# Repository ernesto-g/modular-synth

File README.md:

# Modular synthesizer

Characteristics:

  - Eurorack form factor modules
  - Banana jack connectors
  - 10Vpp audio signals
  - 5V control signals
  - Non standard power connector

# Finished modules

  - [Sequencer](https://github.com/ernesto-g/modular-synth/tree/master/FINISHED/SEQUENCER): 8-step sequencer.
  - [Vintage VCA](https://github.com/ernesto-g/modular-synth/tree/master/FINISHED/VCA): 2-transistor discrete VCA.
  - [Simple VCO](https://github.com/ernesto-g/modular-synth/tree/master/FINISHED/VCO): Triangle and square VCO. 1V/Ocv control voltage.
  - [Slew limiter](https://github.com/ernesto-g/modular-synth/tree/master/FINISHED/SLEW_LIMITER): Slew limiter and LFO
  - [IOs](https://github.com/ernesto-g/modular-synth/tree/master/FINISHED/IOS): Audio line and Eurorack level adapter.
  - [Power Supply](https://github.com/ernesto-g/modular-synth/tree/master/FINISHED/POWER_SUPPLY): Power Supply Board for modules.
  - [Tree](https://github.com/ernesto-g/modular-synth/tree/master/FINISHED/TREE): Banana jack splitter.
  - [Sound Source](https://github.com/ernesto-g/modular-synth/tree/master/FINISHED/SOUND_SOURCE): Macro-oscillator based on Mutable Instruments Braids.
  - [LFOx3](https://github.com/ernesto-g/modular-synth/tree/master/FINISHED/LFOx3): Low frequency oscillator and sequencer.
  - [ATV & Mixer](https://github.com/ernesto-g/modular-synth/tree/master/FINISHED/ATVMixer): Atenuverter X3 and 3-channel mixer.
  - [Simple Sequencer](https://github.com/ernesto-g/modular-synth/tree/master/FINISHED/SIMPLE_SEQUENCER): 4-step sequencer.
  - [Low Pass VCF](https://github.com/ernesto-g/modular-synth/tree/master/FINISHED/VCF): Vactrol VCF.

# Unfinished work

  - Industrial kick
  - Case blueprints
  
# Project structure

Each module has the following structure:

  * Firmware: Microcontroller code (Arduino, Bluepill,etc.)
  * Manual: PDF and DOC file
  * XXXXXXX_modular_PCB: Folder
    * XXXXXXX_modular: Kicad project
    * DIY: PDF files for schematic, PCB and front panel
  * Front Panel Blueprint: Corel Draw files

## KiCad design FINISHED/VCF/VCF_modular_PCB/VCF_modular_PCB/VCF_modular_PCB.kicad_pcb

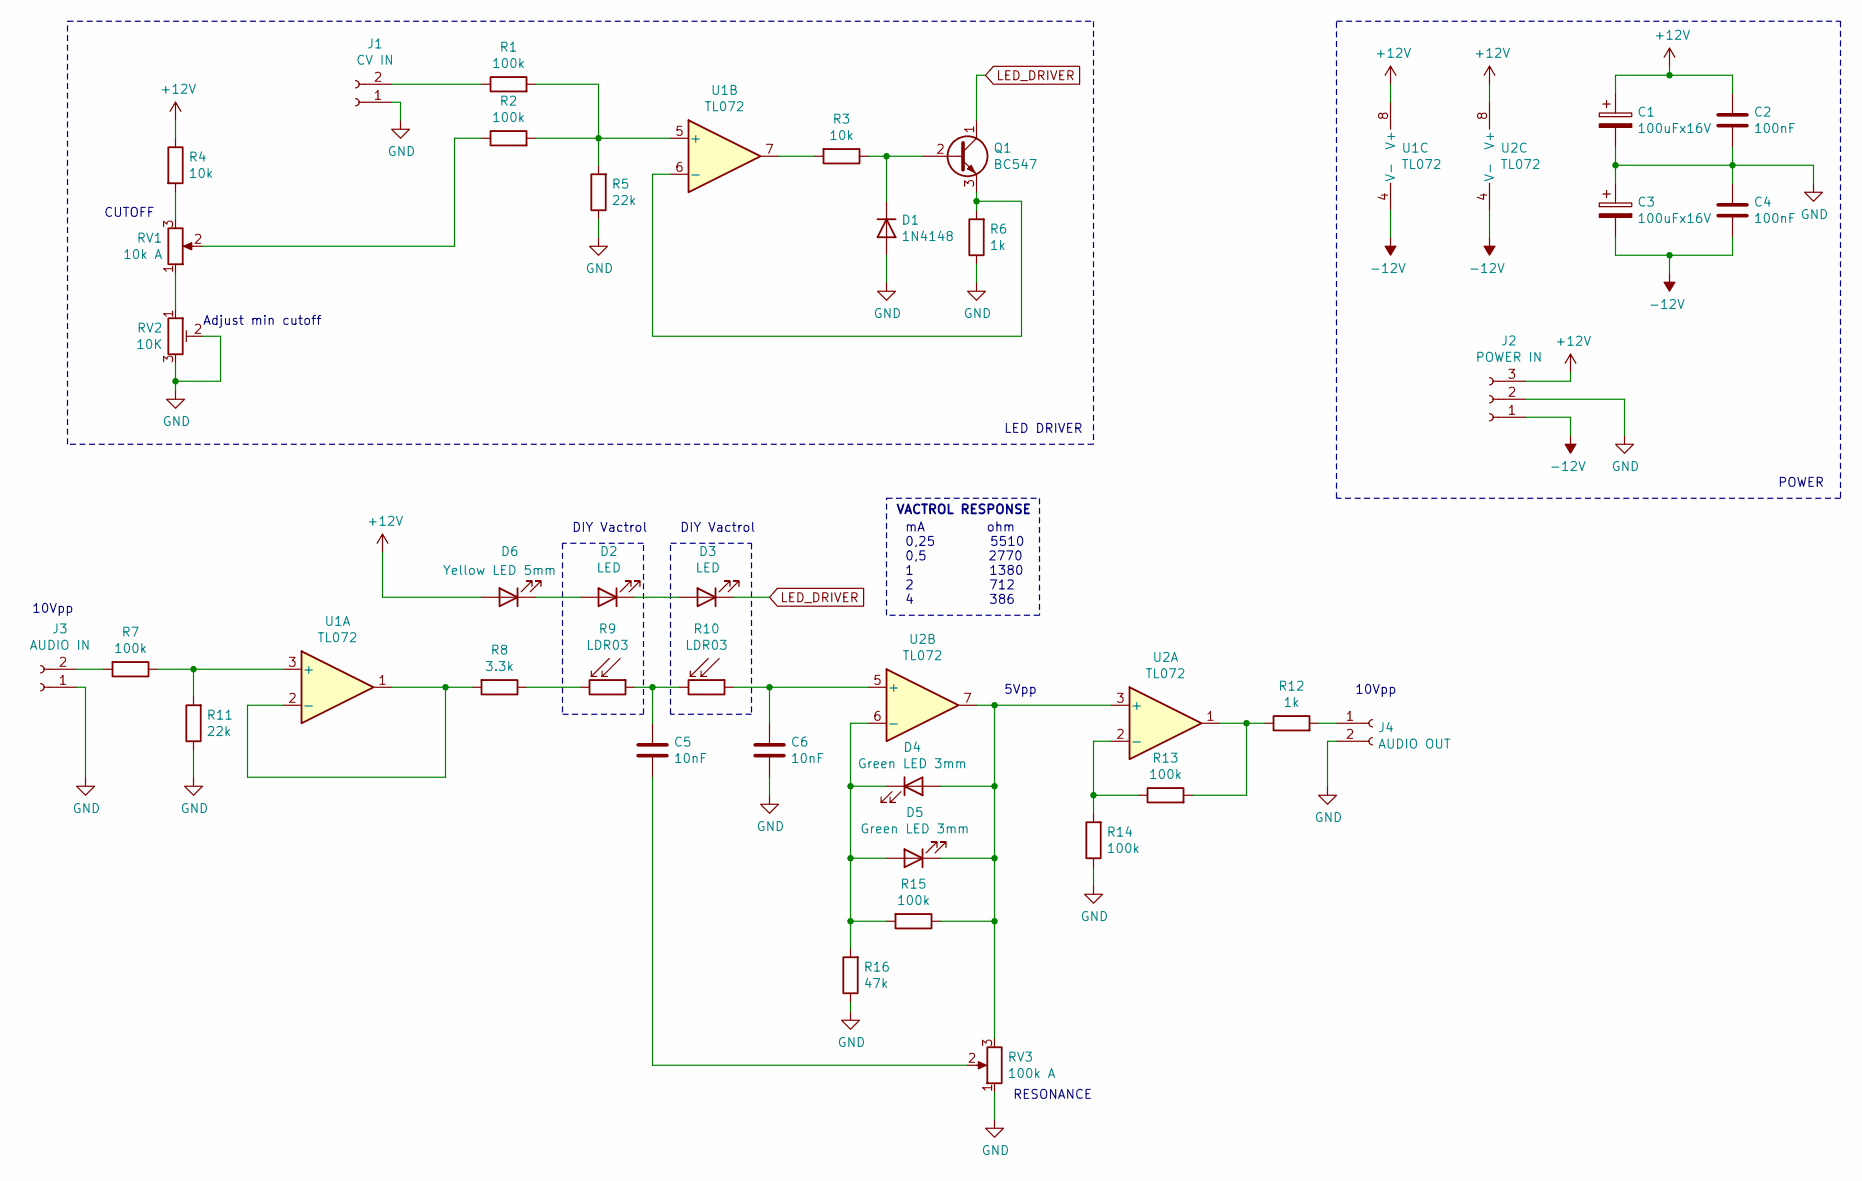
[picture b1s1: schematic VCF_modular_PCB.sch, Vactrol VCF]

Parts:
C1, C3: 100uFx16V; CP_Radial_D6.3mm_P2.50mm
C2, C4: 100nF; C_Disc_D4.7mm_W2.5mm_P5.00mm
C5, C6: 10nF; C_Disc_D4.7mm_W2.5mm_P5.00mm
D1: 1N4148; D_DO-35_SOD27_P7.62mm_Horizontal
D2, D3: LED; LED_D5.0mm_Horizontal_O3.81mm_Z3.0mm
D4, D5: Green LED 3mm; LED_D3.0mm_FlatTop
D6: Yellow LED 5mm; LED_D5.0mm
J1: CV IN; Molex_KK-6410-02_02x2.54mm_Straight
J2: POWER IN; Molex_KK-6410-03_03x2.54mm_Straight
J3: AUDIO IN; Molex_KK-6410-02_02x2.54mm_Straight
J4: AUDIO OUT; Molex_KK-6410-02_02x2.54mm_Straight
Q1: BC547; TO-92_Inline_Wide
R1, R2, R7, R13, R14, R15: 100k; R_Axial_DIN0204_L3.6mm_D1.6mm_P7.62mm_Horizontal
R3, R4: 10k; R_Axial_DIN0204_L3.6mm_D1.6mm_P7.62mm_Horizontal
R5, R11: 22k; R_Axial_DIN0204_L3.6mm_D1.6mm_P7.62mm_Horizontal
R6, R12: 1k; R_Axial_DIN0204_L3.6mm_D1.6mm_P7.62mm_Horizontal
R8: 3.3k; R_Axial_DIN0204_L3.6mm_D1.6mm_P7.62mm_Horizontal
R9, R10: LDR03; Resistor_LDR_Vertical_5.2x5.2_RM3.5
R16: 47k; R_Axial_DIN0204_L3.6mm_D1.6mm_P7.62mm_Horizontal
RV1: 10k A; Potentiometer_Piher_PC-16_Single_Vertical
RV2: 10K; Potentiometer_Trimmer_ACP_CA6v_Horizontal
RV3: 100k A; Potentiometer_Piher_PC-16_Single_Vertical
U1, U2: TL072; DIP-8_W7.62mm_LongPads

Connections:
+12V: C1.1, C2.1, D6.2 (A), J2.3, R4.1, U1.8 (V+), U2.8 (V+)
-12V: C3.2, C4.2, J2.1, U1.4 (V-), U2.4 (V-)
GND: C1.2, C2.2, C3.1, C4.1, C6.2, D1.2 (A), J1.1, J2.2, J3.1, J4.2, R5.1, R6.1, R11.1, R14.1, R16.1, RV2.2, RV2.3, RV3.1
LED_DRIVER: D3.1 (K), Q1.1 (C)
unnamed: C5.1, R9.1, R10.2
unnamed: C5.2, RV3.2
unnamed: C6.1, R10.1, U2.5 (+)
unnamed: D1.1 (K), Q1.2 (B), R3.1
unnamed: D2.1 (K), D3.2 (A)
unnamed: D2.2 (A), D6.1 (K)
unnamed: D4.1 (K), D5.2 (A), R15.2, R16.2, U2.6 (-)
unnamed: D4.2 (A), D5.1 (K), R15.1, RV3.3, U2.3 (+), U2.7
unnamed: J1.2, R1.1
unnamed: J3.2, R7.2
unnamed: J4.1, R12.2
unnamed: Q1.3 (E), R6.2, U1.6 (-)
unnamed: R1.2, R2.2, R5.2, U1.5 (+)
unnamed: R2.1, RV1.2
unnamed: R3.2, U1.7
unnamed: R4.2, RV1.3
unnamed: R8.1, R9.2
unnamed: R8.2, U1.1, U1.2 (-)
unnamed: R7.1, R11.2, U1.3 (+)
unnamed: R12.1, R13.2, U2.1
unnamed: R13.1, R14.2, U2.2 (-)
unnamed: RV1.1, RV2.1

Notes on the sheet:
RESONANCE
DIY Vactrol
CUTOFF
LED DRIVER
POWER
Adjust min cutoff
mA ohm 0,25 5510 0,5 2770 1 1380 2 712 4 386
VACTROL RESPONSE
5Vpp
10Vpp

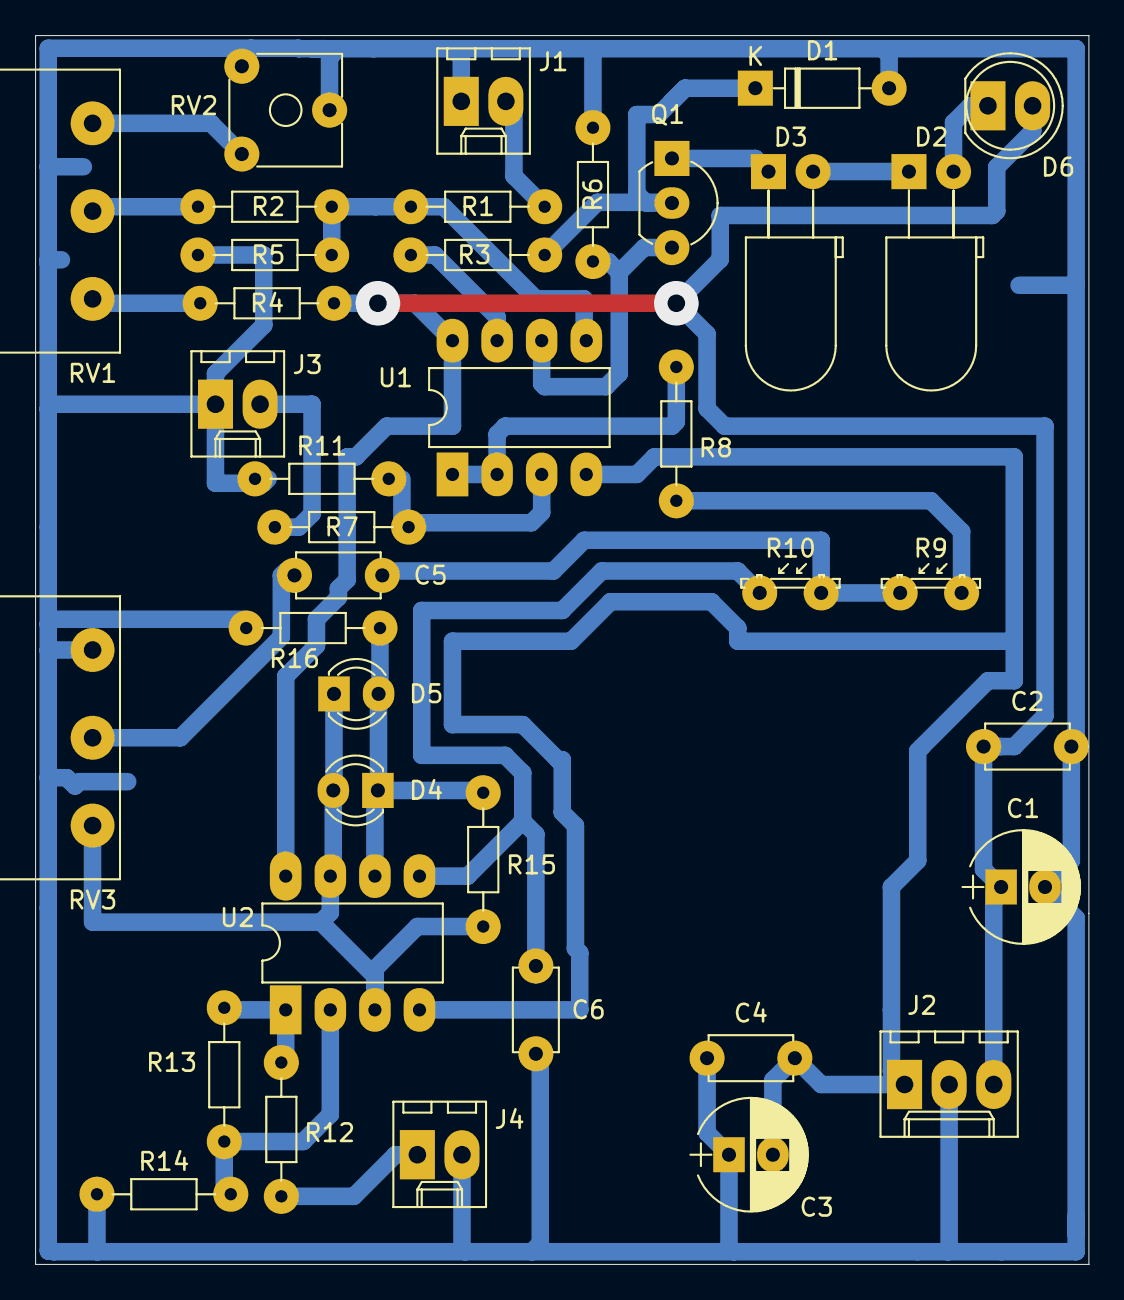
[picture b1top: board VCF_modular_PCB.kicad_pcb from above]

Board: 2 copper layers, 60.0 x 70.0 mm, 38 parts (0 on the bottom side), 26 nets.

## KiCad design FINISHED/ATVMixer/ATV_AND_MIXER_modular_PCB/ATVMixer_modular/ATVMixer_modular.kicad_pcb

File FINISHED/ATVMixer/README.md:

# Atenuverters & 3-channel mixer

Characteristics:

  - Format: Eurorack
  - Dimensions: 8HP, 60mm deep
  - 10Vpp audio signals

# Project structure

  * ATV_AND_MIXER_modular_PCB: Folder
    * ATV_AND_MIXER_modular: Kicad project
    * DIY: PDF files for schematic, PCB and front panel
  * Front Panel Blueprint: Corel Draw files

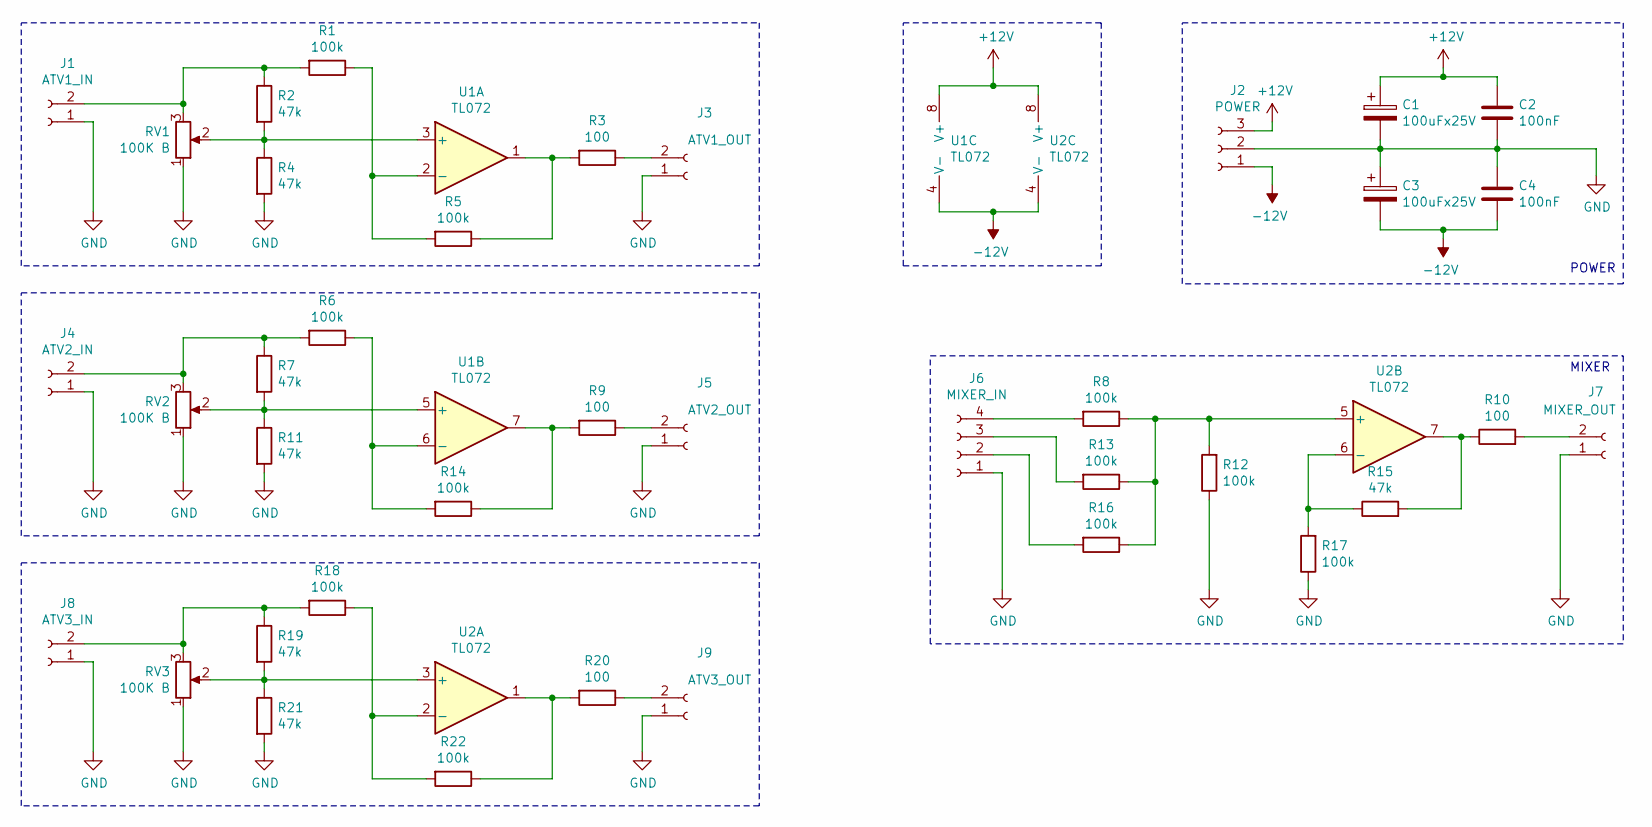
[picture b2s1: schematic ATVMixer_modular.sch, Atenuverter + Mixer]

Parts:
C1, C3: 100uFx25V; CP_Radial_D6.3mm_P2.50mm
C2, C4: 100nF; C_Disc_D4.3mm_W1.9mm_P5.00mm
J1: ATV1_IN; Molex_KK-6410-02_02x2.54mm_Straight
J2: POWER; Molex_KK-6410-03_03x2.54mm_Straight
J3: ATV1_OUT; Molex_KK-6410-02_02x2.54mm_Straight
J4: ATV2_IN; Molex_KK-6410-02_02x2.54mm_Straight
J5: ATV2_OUT; Molex_KK-6410-02_02x2.54mm_Straight
J6: MIXER_IN; Molex_KK-6410-04_04x2.54mm_Straight
J7: MIXER_OUT; Molex_KK-6410-02_02x2.54mm_Straight
J8: ATV3_IN; Molex_KK-6410-02_02x2.54mm_Straight
J9: ATV3_OUT; Molex_KK-6410-02_02x2.54mm_Straight
R1, R5, R6, R8, R12, R13, R14, R16, R17, R18, R22: 100k; R_Axial_DIN0204_L3.6mm_D1.6mm_P7.62mm_Horizontal
R2, R4, R7, R11, R15, R19, R21: 47k; R_Axial_DIN0204_L3.6mm_D1.6mm_P7.62mm_Horizontal
R3, R9, R10, R20: 100; R_Axial_DIN0204_L3.6mm_D1.6mm_P7.62mm_Horizontal
RV1, RV2, RV3: 100K B; Potentiometer_Piher_PC-16_Single_Vertical
U1, U2: TL072; DIP-8_W7.62mm_LongPads

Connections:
+12V: C1.1, C2.1, J2.3, U1.8 (V+), U2.8 (V+)
-12V: C3.2, C4.2, J2.1, U1.4 (V-), U2.4 (V-)
GND: C1.2, C2.2, C3.1, C4.1, J1.1, J2.2, J3.1, J4.1, J5.1, J6.1, J7.1, J8.1, J9.1, R4.2, R11.2, R12.1, R17.1, R21.2, RV1.1, RV2.1, RV3.1
unnamed: J1.2, R1.2, R2.1, RV1.3
unnamed: J3.2, R3.1
unnamed: J4.2, R6.2, R7.1, RV2.3
unnamed: J5.2, R9.1
unnamed: J6.2, R16.2
unnamed: J6.3, R13.2
unnamed: J6.4, R8.2
unnamed: J7.2, R10.2
unnamed: J8.2, R18.2, R19.1, RV3.3
unnamed: J9.2, R20.1
unnamed: R1.1, R5.2, U1.2 (-)
unnamed: R2.2, R4.1, RV1.2, U1.3 (+)
unnamed: R3.2, R5.1, U1.1
unnamed: R10.1, R15.2, U2.7
unnamed: R7.2, R11.1, RV2.2, U1.5 (+)
unnamed: R8.1, R12.2, R13.1, R16.1, U2.5 (+)
unnamed: R9.2, R14.1, U1.7
unnamed: R6.1, R14.2, U1.6 (-)
unnamed: R15.1, R17.2, U2.6 (-)
unnamed: R18.1, R22.2, U2.2 (-), U2.752
unnamed: R19.2, R21.1, RV3.2, U2.3 (+)
unnamed: R20.2, R22.1, U2.1

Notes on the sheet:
MIXER
POWER

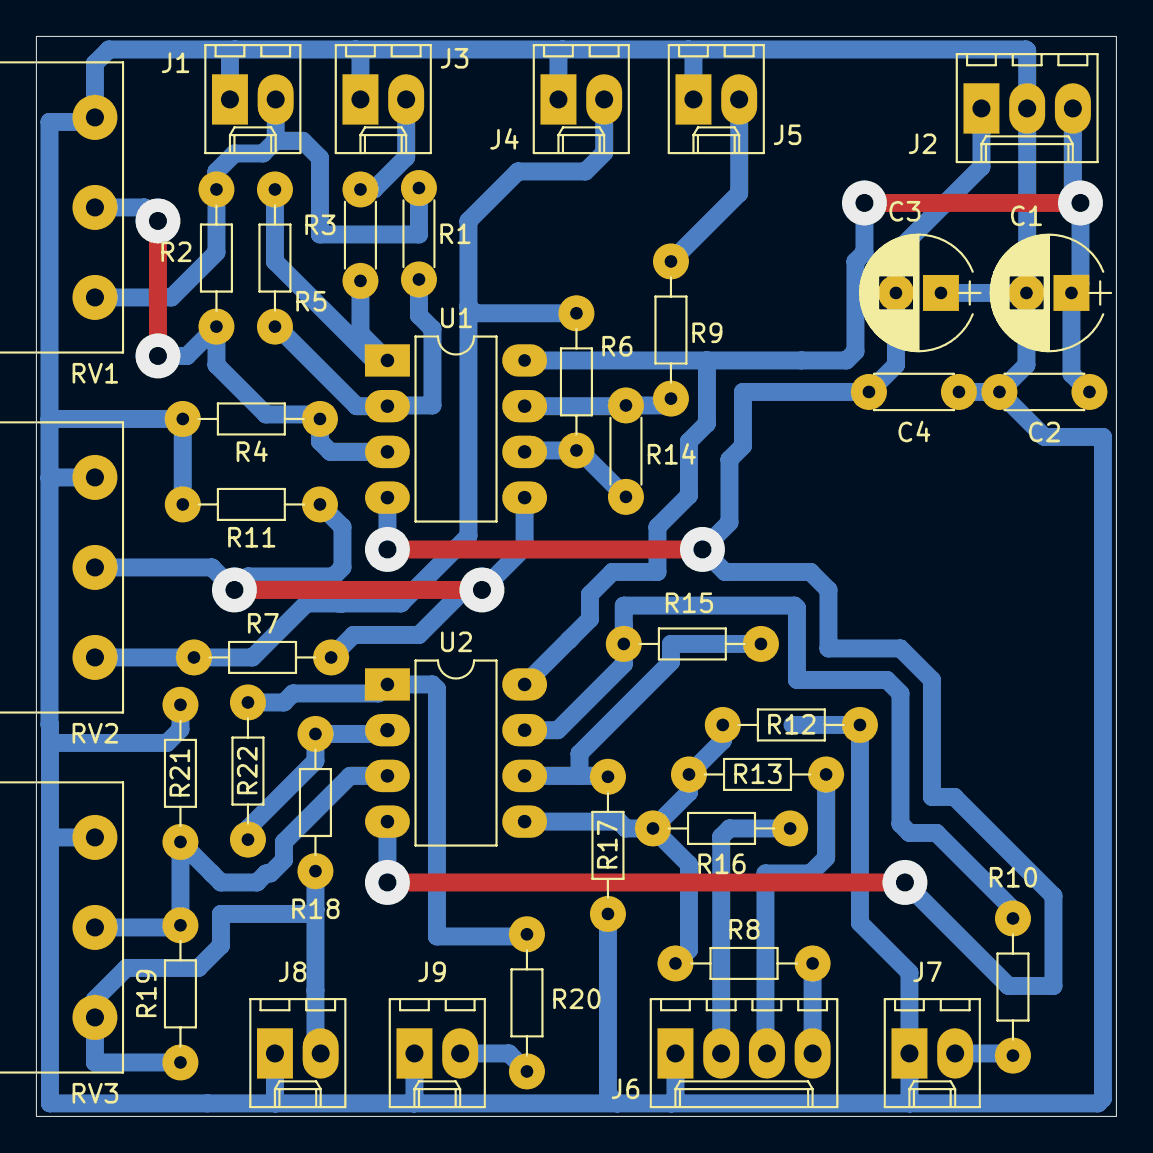
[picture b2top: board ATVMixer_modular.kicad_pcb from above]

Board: 2 copper layers, 60.0 x 60.0 mm, 40 parts (0 on the bottom side), 25 nets.

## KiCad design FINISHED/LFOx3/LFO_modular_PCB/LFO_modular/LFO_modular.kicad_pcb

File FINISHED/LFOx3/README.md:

# LFOx3: Low frequency oscillator
LFOx3 is a 3 channel digital low frequency oscillator module.

Characteristics:

  - Format: Eurorack
  - Dimensions: 8HP, 60mm deep
  - 10Vpp audio signals
  - 5V control signals
  - 5 Waveforms
  - 105sec to 150Hz range.
  - 10kHz, 8-bit audio processing
  - Beginning of cycle Output.

Download [manual](https://github.com/ernesto-g/modular-synth/raw/master/FINISHED/LFOx3/Manual/LFOx3%20Manual.pdf)   
 
# Project structure

  * Firmware: Code for Arduino nano
  * Manual: PDF and DOC file
  * LFO_modular_PCB: Folder
    * LFO_modular: Kicad project
    * DIY: PDF files for schematic, PCB and front panel
  * Front Panel Blueprint: Corel Draw files

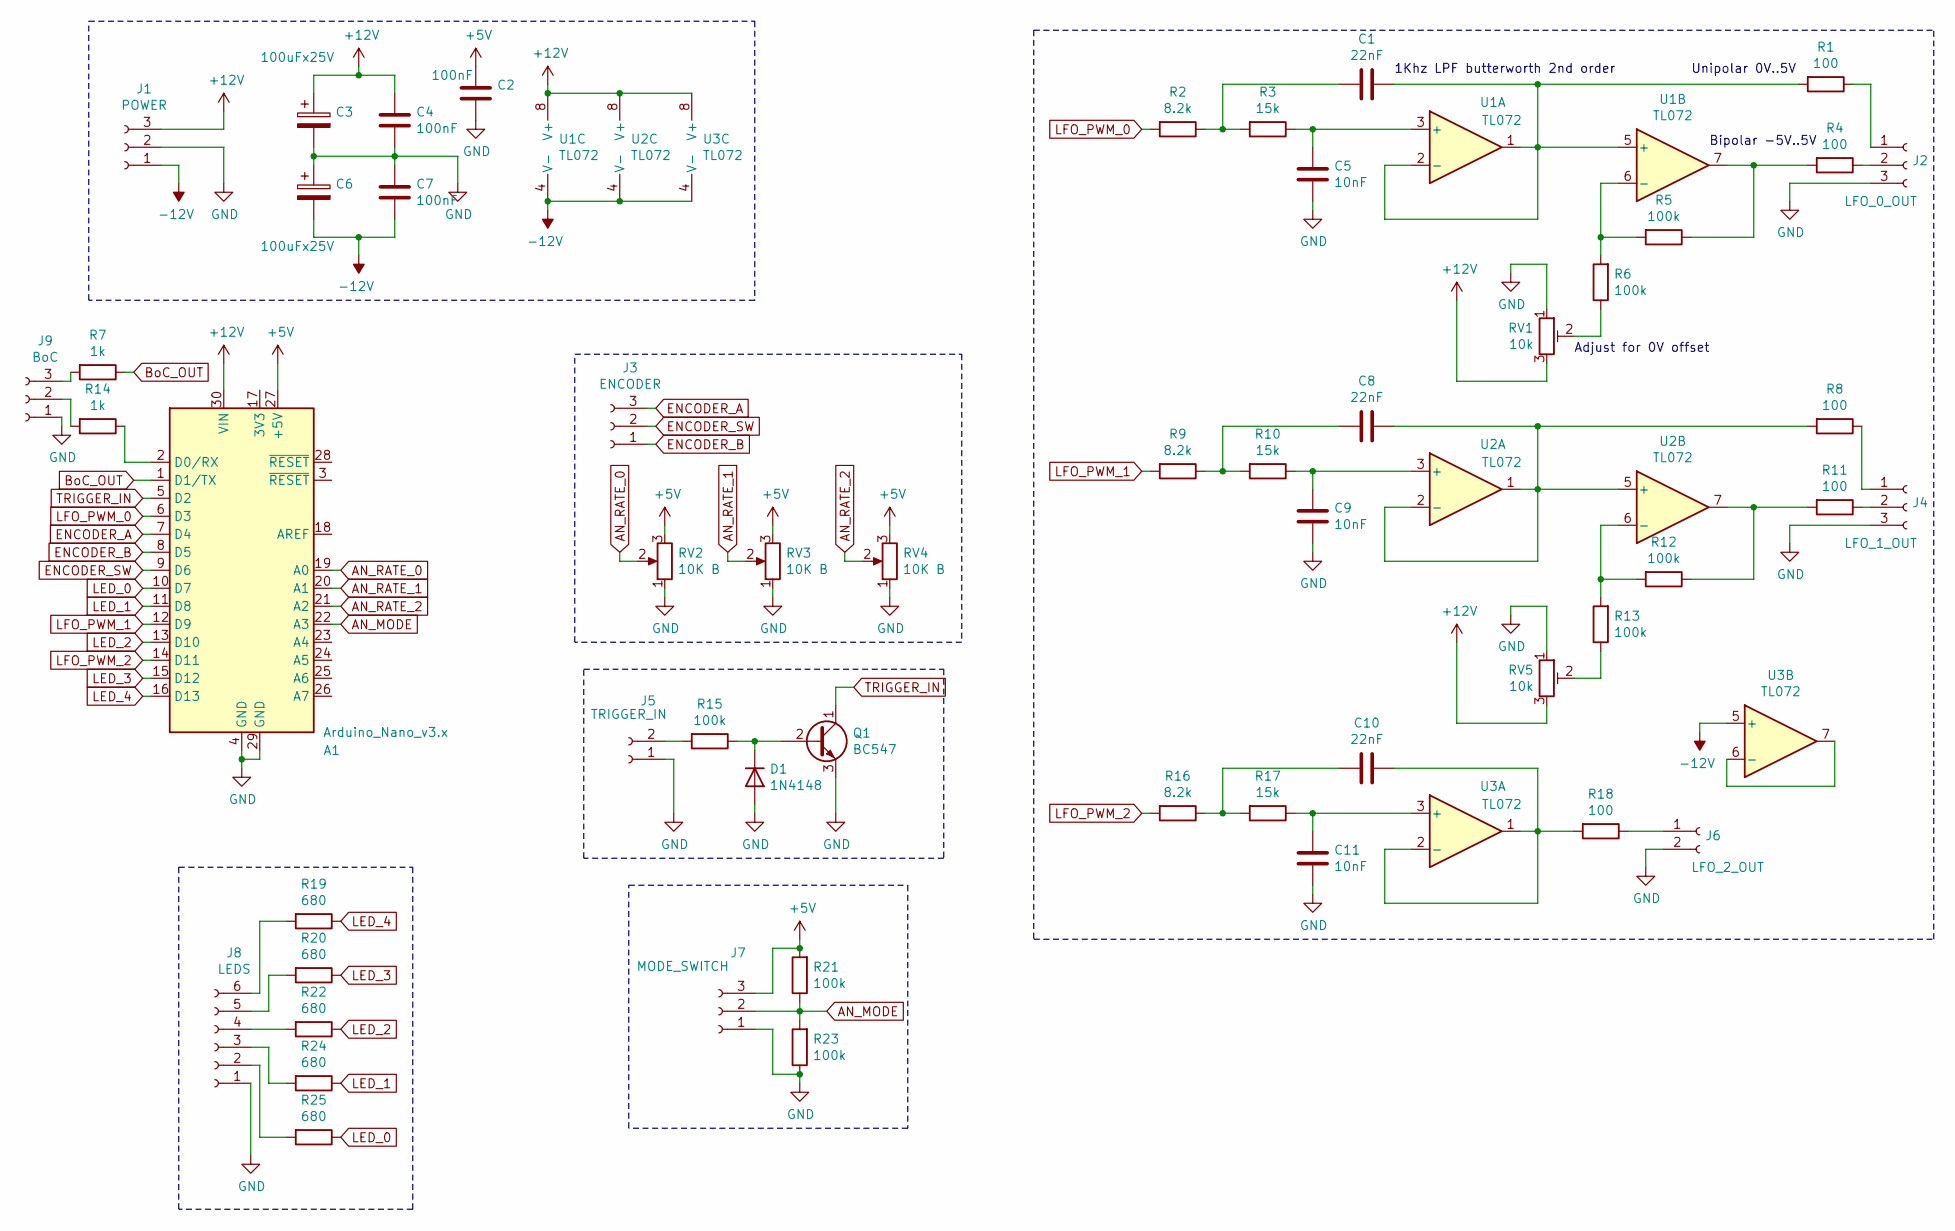
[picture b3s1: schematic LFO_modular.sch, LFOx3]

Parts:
A1: Arduino_Nano_v3.x; Arduino_Nano
C1, C8, C10: 22nF; C_Disc_D4.7mm_W2.5mm_P5.00mm
C2, C4, C7: 100nF; C_Disc_D4.7mm_W2.5mm_P5.00mm
C3, C6: 100uFx25V; CP_Radial_D6.3mm_P2.50mm
C5, C9, C11: 10nF; C_Disc_D4.7mm_W2.5mm_P5.00mm
D1: 1N4148; D_DO-35_SOD27_P7.62mm_Horizontal
J1: POWER; Molex_KK-6410-03_03x2.54mm_Straight
J2: LFO_0_OUT; Molex_KK-6410-03_03x2.54mm_Straight
J3: ENCODER; Molex_KK-6410-03_03x2.54mm_Straight
J4: LFO_1_OUT; Molex_KK-6410-03_03x2.54mm_Straight
J5: TRIGGER_IN; Molex_KK-6410-02_02x2.54mm_Straight
J6: LFO_2_OUT; Molex_KK-6410-02_02x2.54mm_Straight
J7: MODE_SWITCH; Molex_KK-6410-03_03x2.54mm_Straight
J8: LEDS; Molex_KK-6410-06_06x2.54mm_Straight
J9: BoC; Molex_KK-6410-03_03x2.54mm_Straight
Q1: BC547; TO-92_HandSolder
R1, R4, R8, R11, R18: 100; R_Axial_DIN0204_L3.6mm_D1.6mm_P7.62mm_Horizontal
R2, R9, R16: 8.2k; R_Axial_DIN0204_L3.6mm_D1.6mm_P7.62mm_Horizontal
R3, R10, R17: 15k; R_Axial_DIN0204_L3.6mm_D1.6mm_P7.62mm_Horizontal
R5, R6, R12, R13, R15, R21, R23: 100k; R_Axial_DIN0204_L3.6mm_D1.6mm_P7.62mm_Horizontal
R7, R14: 1k; R_Axial_DIN0204_L3.6mm_D1.6mm_P7.62mm_Horizontal
R19, R20, R22, R24, R25: 680; R_Axial_DIN0204_L3.6mm_D1.6mm_P7.62mm_Horizontal
RV1, RV5: 10k; Potentiometer_Trimmer_ACP_CA6v_Horizontal
RV2, RV3, RV4: 10K B; Potentiometer_Piher_PC-16_Single_Vertical
U1, U2, U3: TL072; DIP-8_W7.62mm_LongPads

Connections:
+5V: A1.27 (+5V), C2.1, J7.3, R21.2, RV2.3, RV3.3, RV4.3
+12V: A1.30 (VIN), C3.1, C4.1, J1.3, RV1.3, RV5.3, U1.8 (V+), U2.8 (V+), U3.8 (V+)
-12V: C6.2, C7.2, J1.1, U1.4 (V-), U2.4 (V-), U3.4 (V-), U3.5 (+)
AN_MODE: A1.22 (A3), J7.2, R21.1, R23.2
AN_RATE_0: A1.19 (A0), RV2.2
AN_RATE_1: A1.20 (A1), RV3.2
AN_RATE_2: A1.21 (A2), RV4.2
ENCODER_A: A1.7 (D4), J3.3
ENCODER_B: A1.8 (D5), J3.1
ENCODER_SW: A1.9 (D6), J3.2
GND: A1.4 (GND), A1.29 (GND), C2.2, C3.2, C4.2, C5.2, C6.1, C7.1, C9.2, C11.2, D1.2 (A), J1.2, J2.3, J4.3, J5.1, J6.2, J7.1, J8.1, J9.1, Q1.3 (E), R23.1, RV1.1, RV2.1, RV3.1, RV4.1, RV5.1
LED_0: A1.10 (D7), R25.1
LED_1: A1.11 (D8), R24.1
LED_2: A1.13 (D10), R22.1
LED_3: A1.15 (D12), R20.1
LED_4: A1.16 (D13), R19.1
LFO_PWM_0: A1.6 (D3), R2.2
LFO_PWM_1: A1.12 (D9), R9.2
LFO_PWM_2: A1.14 (D11), R16.2
unnamed: A1.1 (D1/TX), R7.1
unnamed: A1.2 (D0/RX), R14.1
unnamed: C1.1, R1.2, U1.1, U1.2 (-), U1.5 (+)
unnamed: C1.2, R2.1, R3.2
unnamed: C5.1, R3.1, U1.3 (+)
unnamed: C8.1, R8.2, U2.1, U2.2 (-), U2.5 (+)
unnamed: C8.2, R9.1, R10.2
unnamed: C9.1, R10.1, U2.3 (+)
unnamed: C10.1, R18.2, U3.1, U3.2 (-)
unnamed: C10.2, R16.1, R17.2
unnamed: C11.1, R17.1, U3.3 (+)
unnamed: D1.1 (K), Q1.2 (B), R15.1
unnamed: J2.1, R1.1
unnamed: J2.2, R4.1
unnamed: J4.1, R8.1
unnamed: J4.2, R11.1
unnamed: J5.2, R15.2
unnamed: J6.1, R18.1
unnamed: J8.2, R25.2
unnamed: J8.3, R24.2
unnamed: J8.4, R22.2
unnamed: J8.5, R20.2
unnamed: J8.6, R19.2
unnamed: J9.2, R14.2
unnamed: J9.3, R7.2
unnamed: R4.2, R5.1, U1.7
unnamed: R5.2, R6.2, U1.6 (-)
unnamed: R6.1, RV1.2
unnamed: R11.2, R12.1, U2.7
unnamed: R12.2, R13.2, U2.6 (-)
unnamed: R13.1, RV5.2
unnamed: U3.6 (-), U3.7
TRIGGER_IN: A1.5 (D2), Q1.1 (C)

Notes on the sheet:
Unipolar 0V..5V
Bipolar -5V..5V
1Khz LPF butterworth 2nd order
Adjust for 0V offset

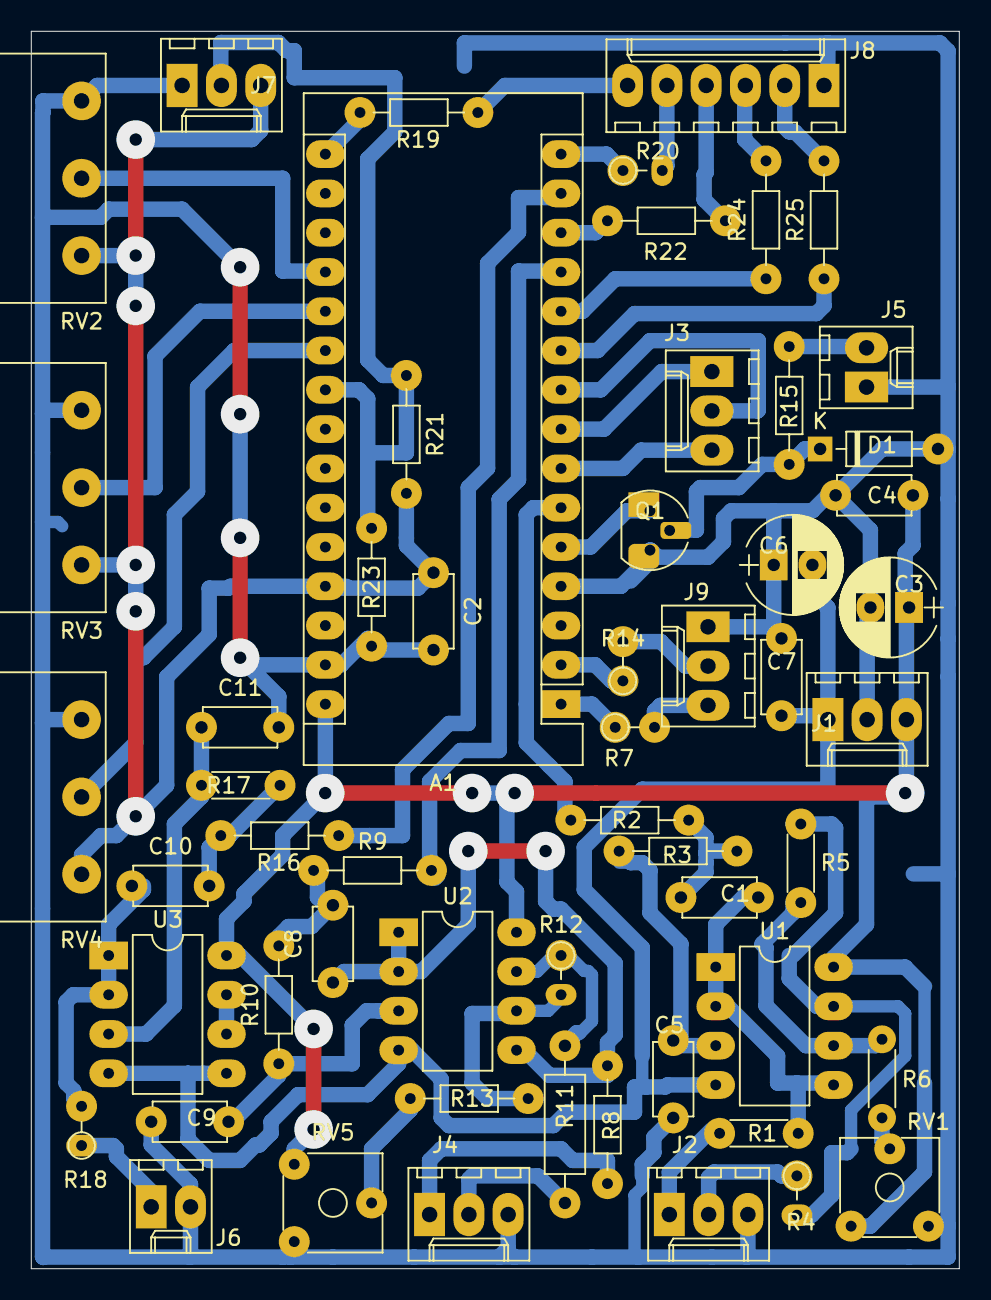
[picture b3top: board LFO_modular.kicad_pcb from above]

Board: 2 copper layers, 60.0 x 80.0 mm, 56 parts (0 on the bottom side), 52 nets.

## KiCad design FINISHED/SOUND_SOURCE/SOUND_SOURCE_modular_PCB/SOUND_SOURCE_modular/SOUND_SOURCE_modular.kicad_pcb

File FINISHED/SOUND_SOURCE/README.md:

# Sound Source: Macro-oscillator
Sound Source is a voltage-controlled monophonic digital oscillator. Each algorithm is controlled by two continuously variable parameters, TIMBRE and COLOR, both of them voltage controllable.

This project is based on Mutable Intruments [Braids](https://mutable-instruments.net/modules/braids). 
The code was adapted for [Blue Pill](https://stm32-base.org/boards/STM32F103C8T6-Blue-Pill.html) microcontroller.

Characteristics:

  - Format: Eurorack
  - Dimensions: 12HP, 80mm deep
  - 10Vpp audio signals
  - 5V control signals
  - 43 Waveforms
  - 96kHz, 8-bit audio processing
  - 12-bit CV capture.

Download [manual](https://github.com/ernesto-g/modular-synth/raw/master/FINISHED/SOUND_SOURCE/Manual/Sound%20Source%20Manual.pdf)   
 
# Project structure

  * Firmware: Code for Blue Pill using ST Cube IDE
  * Manual: PDF and DOC file
  * SOUND_SOURCE_modular_PCB: Folder
    * SOUND_SOURCE_modular: Kicad project
    * DIY: PDF files for schematic, PCB and front panel
  * Front Panel Blueprint: Corel Draw files

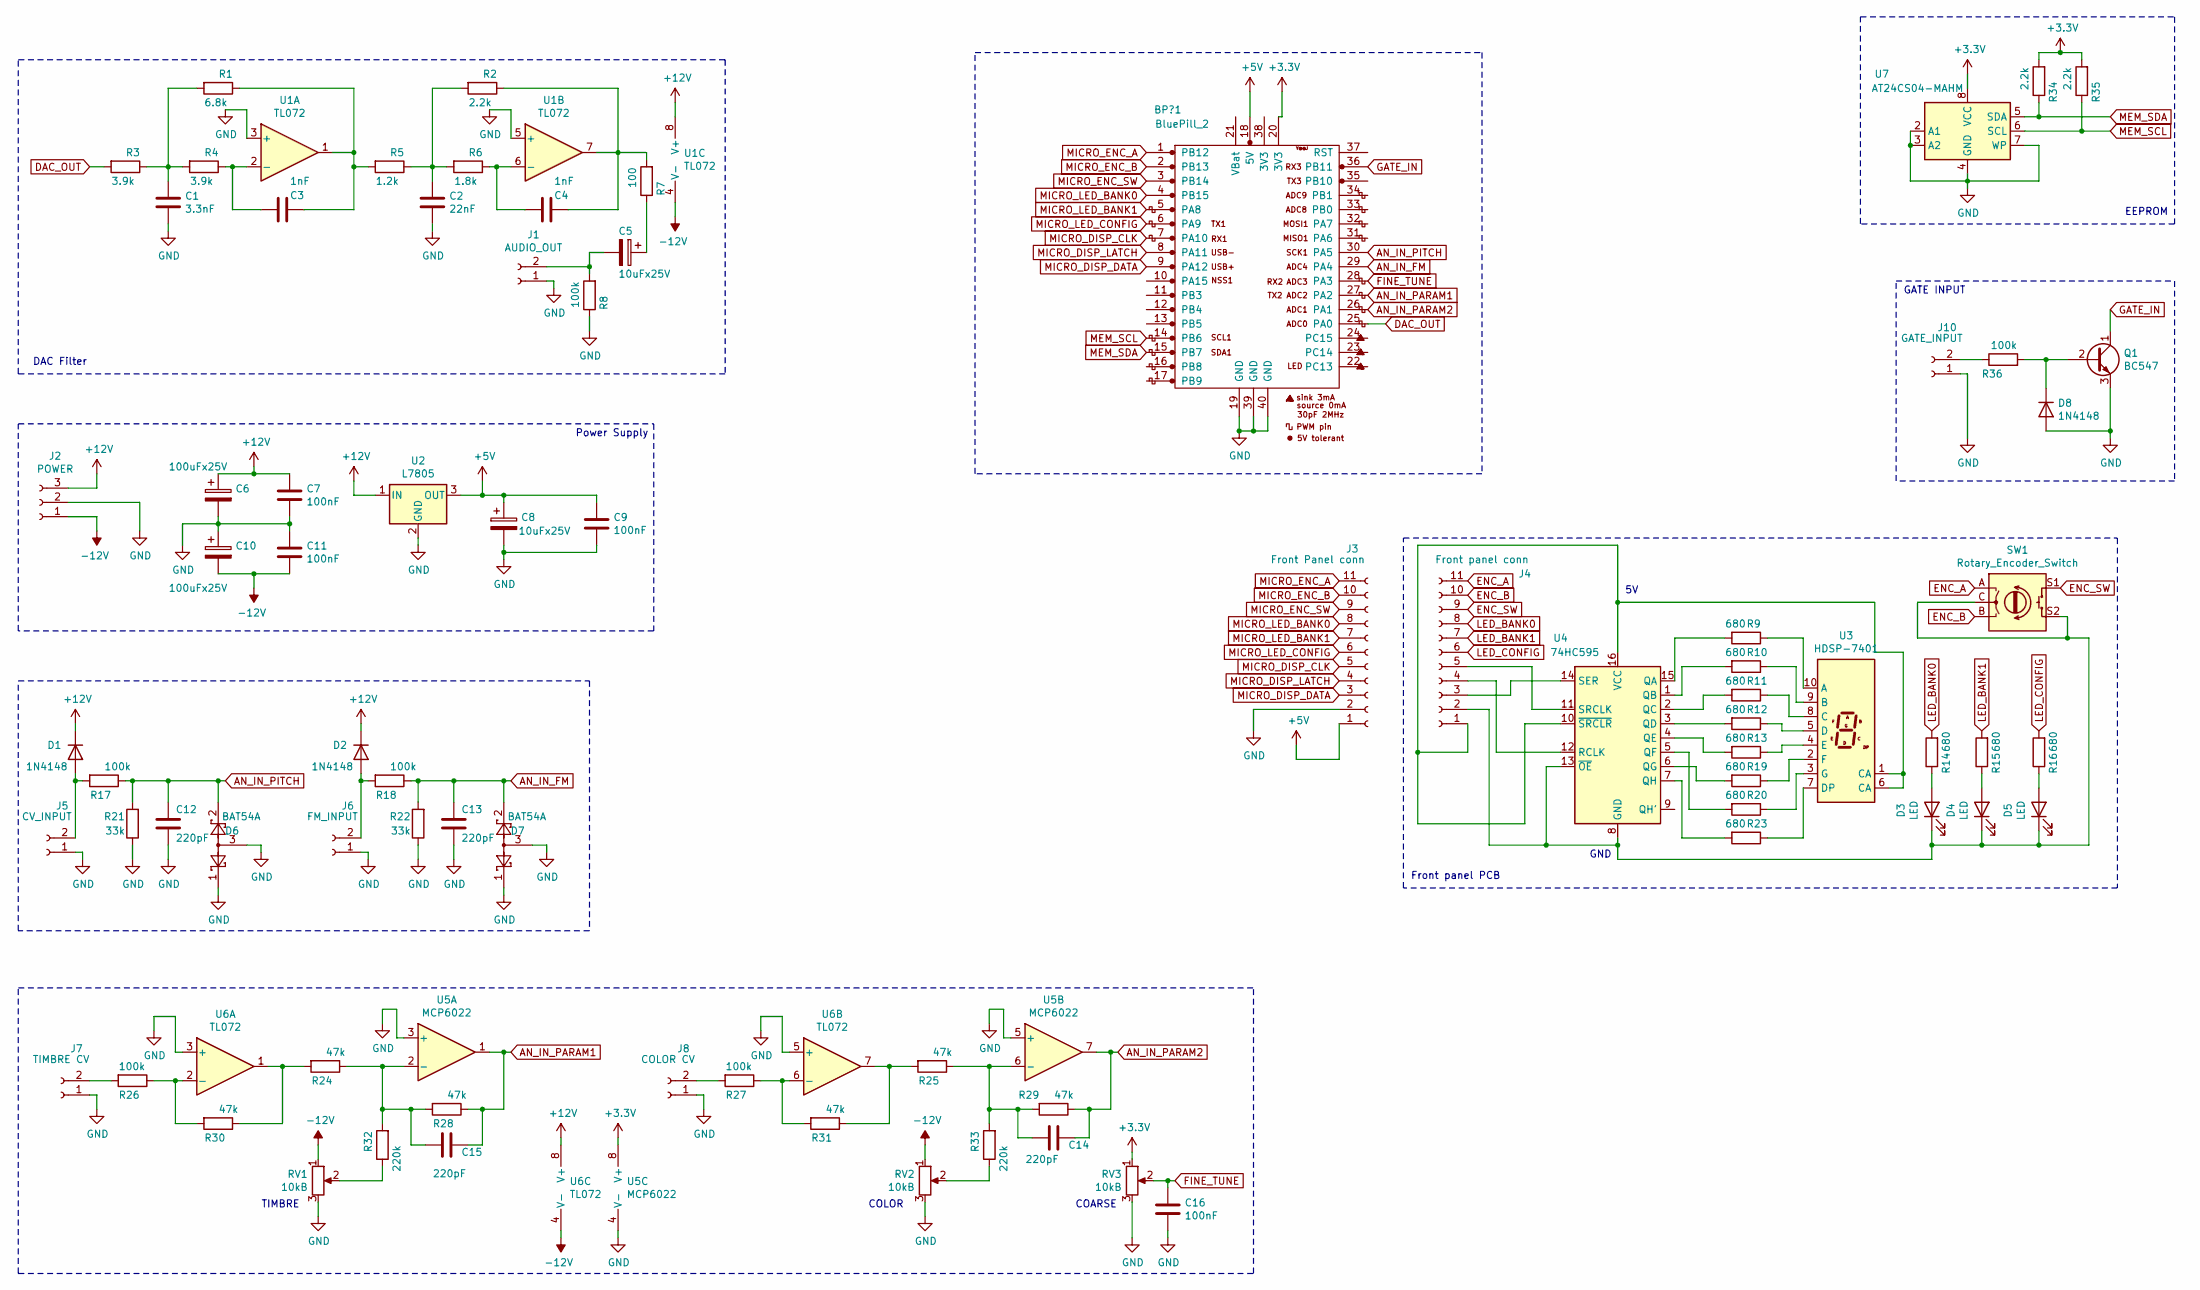
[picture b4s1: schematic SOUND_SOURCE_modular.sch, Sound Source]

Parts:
BP?1: BluePill_2; YAAJ_BluePill
C1: 3.3nF; C_Disc_D4.3mm_W1.9mm_P5.00mm
C2: 22nF; C_Disc_D4.3mm_W1.9mm_P5.00mm
C3, C4: 1nF; C_Disc_D4.3mm_W1.9mm_P5.00mm
C5, C8: 10uFx25V; CP_Radial_D5.0mm_P2.50mm
C6, C10: 100uFx25V; CP_Radial_D6.3mm_P2.50mm
C7, C9, C11, C16: 100nF; C_Disc_D4.3mm_W1.9mm_P5.00mm
C12, C13, C14, C15: 220pF; C_Disc_D4.3mm_W1.9mm_P5.00mm
D1, D2, D8: 1N4148; D_DO-35_SOD27_P7.62mm_Horizontal
D3, D4, D5: LED; LED_D3.0mm
D6, D7: BAT54A; SOT-23
J1: AUDIO_OUT; Molex_KK-6410-02_02x2.54mm_Straight
J2: POWER; Molex_KK-6410-03_03x2.54mm_Straight
J3: Front Panel conn; Molex_KK-6410-11_11x2.54mm_Straight
J4: Front panel conn; Molex_KK-6410-11_11x2.54mm_Straight
J5: CV_INPUT; Molex_KK-6410-02_02x2.54mm_Straight
J6: FM_INPUT; Molex_KK-6410-02_02x2.54mm_Straight
J7: TIMBRE CV; Molex_KK-6410-02_02x2.54mm_Straight
J8: COLOR CV; Molex_KK-6410-02_02x2.54mm_Straight
J10: GATE_INPUT; Molex_KK-6410-02_02x2.54mm_Straight
Q1: BC547; TO-92_Inline
R1: 6.8k; R_Axial_DIN0204_L3.6mm_D1.6mm_P7.62mm_Horizontal
R2, R34, R35: 2.2k; R_Axial_DIN0204_L3.6mm_D1.6mm_P7.62mm_Horizontal
R3, R4: 3.9k; R_Axial_DIN0204_L3.6mm_D1.6mm_P7.62mm_Horizontal
R5: 1.2k; R_Axial_DIN0204_L3.6mm_D1.6mm_P7.62mm_Horizontal
R6: 1.8k; R_Axial_DIN0204_L3.6mm_D1.6mm_P7.62mm_Horizontal
R7: 100; R_Axial_DIN0204_L3.6mm_D1.6mm_P7.62mm_Horizontal
R8, R17, R18, R26, R27, R36: 100k; R_Axial_DIN0204_L3.6mm_D1.6mm_P7.62mm_Horizontal
R9, R10, R11, R12, R13, R14, R15, R16, R19, R20, R23: 680; R_Axial_DIN0204_L3.6mm_D1.6mm_P7.62mm_Horizontal
R21, R22: 33k; R_Axial_DIN0204_L3.6mm_D1.6mm_P7.62mm_Horizontal
R24, R25, R28, R29, R30, R31: 47k; R_Axial_DIN0204_L3.6mm_D1.6mm_P7.62mm_Horizontal
R32, R33: 220k; R_Axial_DIN0204_L3.6mm_D1.6mm_P7.62mm_Horizontal
RV1, RV2, RV3: 10kB; Potentiometer_Piher_PC-16_Single_Vertical
SW1: Rotary_Encoder_Switch; RotaryEncoder_Alps_EC11E-Switch_Vertical_H20mm
U1, U6: TL072; DIP-8_W7.62mm_Socket_LongPads
U2: L7805; TO-220-3_Vertical
U3: HDSP-7401
U4: 74HC595; SOIC-16_3.9x9.9mm_Pitch1.27mm
U5: MCP6022; DIP-8_W7.62mm_Socket_LongPads
U7: AT24CS04-MAHM; DIP-8_W7.62mm_Socket_LongPads

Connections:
+3V3: BP?1.20 (3V3), R34.2, R35.2, RV3.1, U5.8 (V+), U7.8 (VCC)
+5V: BP?1.18 (5V), C8.1, C9.1, J3.1, U2.3 (OUT)
+12V: C6.1, C7.1, D1.1 (K), D2.1 (K), J2.3, U1.8 (V+), U2.1 (IN), U6.8 (V+)
-12V: C10.2, C11.2, J2.1, RV1.1, RV2.1, U1.4 (V-), U6.4 (V-)
AN_IN_FM: BP?1.29 (PA4), C13.1, D7.2, R18.1, R22.2
AN_IN_PARAM1: BP?1.27 (PA2), C15.1, R28.1, U5.1
AN_IN_PARAM2: BP?1.26 (PA1), C14.1, R29.1, U5.7
AN_IN_PITCH: BP?1.30 (PA5), C12.1, D6.2, R17.1, R21.2
DAC_OUT: BP?1.25 (PA0), R3.2
ENC_A: J4.11, SW1.A
ENC_B: J4.10, SW1.B
ENC_SW: J4.9, SW1.S1
FINE_TUNE: BP?1.28 (PA3), C16.1, RV3.2
GATE_IN: BP?1.36 (PB11), Q1.1 (C)
GND: BP?1.19 (GND), BP?1.39 (GND), BP?1.40 (GND), C1.2, C2.2, C6.2, C7.2, C8.2, C9.2, C10.1, C11.1, C12.2, C13.2, C16.2, D6.1, D6.3, D7.1, D7.3, D8.2 (A), J1.1, J2.2, J3.2, J5.1, J6.1, J7.1, J8.1, J10.1, Q1.3 (E), R8.1, R21.1, R22.1, RV1.3, RV2.3, RV3.3, U1.3 (+), U1.5 (+), U2.2 (GND), U5.3 (+), U5.4 (V-), U5.5 (+), U6.3 (+), U6.5 (+), U7.2 (A1), U7.3 (A2), U7.4 (GND), U7.7 (WP)
LED_BANK0: J4.8, R14.2
LED_BANK1: J4.7, R15.2
LED_CONFIG: J4.6, R16.2
MEM_SCL: BP?1.14 (PB6), R35.1, U7.6 (SCL)
MEM_SDA: BP?1.15 (PB7), R34.1, U7.5 (SDA)
MICRO_DISP_CLK: BP?1.7 (PA10), J3.5
MICRO_DISP_DATA: BP?1.9 (PA12), J3.3
MICRO_DISP_LATCH: BP?1.8 (PA11), J3.4
MICRO_ENC_A: BP?1.1 (PB12), J3.11
MICRO_ENC_B: BP?1.2 (PB13), J3.10
MICRO_ENC_SW: BP?1.3 (PB14), J3.9
MICRO_LED_BANK0: BP?1.4 (PB15), J3.8
MICRO_LED_BANK1: BP?1.5 (PA8), J3.7
MICRO_LED_CONFIG: BP?1.6 (PA9), J3.6
unnamed: C1.1, R1.2, R3.1, R4.2
unnamed: C2.1, R2.2, R5.1, R6.2
unnamed: C3.1, R1.1, R5.2, U1.1
unnamed: C3.2, R4.1, U1.2 (-)
unnamed: C4.1, R2.1, R7.2, U1.7
unnamed: C4.2, R6.1, U1.6 (-)
unnamed: C5.1, R7.1
unnamed: C5.2, J1.2, R8.2
unnamed: C14.2, R25.1, R29.2, R33.2, U5.6 (-)
unnamed: C15.2, R24.1, R28.2, R32.2, U5.2 (-)
unnamed: D1.2 (A), J5.2, R17.2
unnamed: D2.2 (A), J6.2, R18.2
unnamed: D3.1 (K), D4.1 (K), D5.1 (K), J4.2, SW1.C, SW1.S2, U4.8 (GND), U4.13 (~OE)
unnamed: D3.2 (A), R14.1
unnamed: D4.2 (A), R15.1
unnamed: D5.2 (A), R16.1
unnamed: D8.1 (K), Q1.2 (B), R36.2
unnamed: J4.1, U3.1 (CA), U3.6 (CA), U4.10 (~SRCLR), U4.16 (VCC)
unnamed: J4.3, U4.14 (SER)
unnamed: J4.4, U4.12 (RCLK)
unnamed: J4.5, U4.11 (SRCLK)
unnamed: J7.2, R26.2
unnamed: J8.2, R27.2
unnamed: J10.2, R36.1
unnamed: R9.1, U3.10 (A)
unnamed: R9.2, U4.15 (QA)
unnamed: R10.1, U3.9 (B)
unnamed: R10.2, U4.1 (QB)
unnamed: R11.1, U3.8 (C)
unnamed: R11.2, U4.2 (QC)
unnamed: R12.1, U3.5 (D)
unnamed: R12.2, U4.3 (QD)
unnamed: R13.1, U3.4 (E)
unnamed: R13.2, U4.4 (QE)
unnamed: R19.1, U3.2 (F)
unnamed: R19.2, U4.6 (QG)
unnamed: R20.1, U3.3 (G)
unnamed: R20.2, U4.5 (QF)
unnamed: R23.1, U3.7 (DP)
unnamed: R23.2, U4.7 (QH)
unnamed: R24.2, R30.1, U6.1
unnamed: R25.2, R31.1, U6.7
unnamed: R26.1, R30.2, U6.2 (-)
unnamed: R27.1, R31.2, U6.6 (-)
unnamed: R32.1, RV1.2
unnamed: R33.1, RV2.2

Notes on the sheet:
Power Supply
DAC Filter
Front panel PCB
COARSE
TIMBRE
COLOR
EEPROM
GATE INPUT
GND
